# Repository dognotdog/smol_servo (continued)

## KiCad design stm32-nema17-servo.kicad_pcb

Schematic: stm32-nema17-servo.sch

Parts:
C1, C2, C3, C4, C5, C6, C7, C8, C9, C18: 100n; C_0402_1005Metric
C10, C12, C23, C24: 10u 60V; C_1210_3225Metric
C11, C13: 100n 60V; C_0402_1005Metric
C14, C22: 10u 20V; C_0805_2012Metric
C15: 1u 16V; C_0603_1608Metric
C16: 47n 60V; C_0603_1608Metric
C17: 1u 6.3V; C_0402_1005Metric
C19: 22u 5V; C_0805_2012Metric
C20: 100n 16V; C_0402_1005Metric
C21: 100n 20V; C_0402_1005Metric
D1, D2: 1A; D_0402_1005Metric
D3: IN-S128TATRGB; LED_Kingbright_AAA3528ESGCT
D4: 3.3V 1mA; D_0402_1005Metric
H1: M3; MountingHole_3.2mm_M3_DIN965_Pad
H2, H3, H4: M3; MountingHole_3.2mm_M3
J1: Conn_01x05; PinHeader_1x06_P2.54mm_Vertical
J2: C31-S-RA-CS1A-BK-SS; USB_C_Receptacle_Adam_C31-S-RA-CS1A-BK-SS
J3: TC-2050; Tag-Connect_TC2050-IDC-NL_2x05_P1.27mm_Vertical
J4, J5: Screw_Terminal_01x02; TerminalBlock_Phoenix_PT-1,5-2-3.5-H_1x02_P3.50mm_Horizontal
J7, J8: Conn_01x03; PinHeader_1x03_P2.54mm_Vertical
J9: Conn_01x02; PinHeader_1x02_P2.54mm_Vertical
L1, L3: BLM18PG471SN1D; L_0603_1608Metric
L2: 2.2uH 1.6A; L_0806_2016Metric
L4: 22uH 1.6A; L_Taiyo-Yuden_NR-50xx
M1: Stepper_Motor_bipolar; PinHeader_1x04_P2.54mm_Vertical
Q1: NTTFS4937N; WDFN8
Q2, Q3, Q4, Q5, Q6, Q7: NVTFS5C658NL; WDFN8
Q8, Q9, Q10: SSM3K35CTC; SOT-883
R1, R2, R3: 680R; R_0402_1005Metric
R4, R5: 5K1; R_0402_1005Metric
R6: 2.2R; R_0402_1005Metric
R7, R8, R27: 100K; R_0402_1005Metric
R9, R10, R11: 15m; R_1206_3216Metric
R12, R28: 120K; R_0402_1005Metric
R13: 10K; R_0402_1005Metric
R14, R15, R16: 100R; R_0402_1005Metric
R17: 430R; R_0402_1005Metric
R18, R19: 470R; R_0402_1005Metric
R20, R21, R22, R23, R24, R25, R26: 1K; R_0402_1005Metric
R29: 5K; R_0402_1005Metric
SW1: EVP-BB2A9B000; SW_SPST_EVPBB
U1: STM32G431CBU; QFN-48-1EP_7x7mm_P0.5mm_EP5.6x5.6mm_ThermalVias
U2: 74LVC2G32; X2SON-8_1.4x1mm_P0.35mm
U3: UCC27516; Texas_PWSON-N6
U4: AS5047D; TSSOP-14_4.4x5mm_P0.65mm-inlaid
U5: TPS62172DSG; WSON-8-1EP_2x2mm_P0.5mm_EP0.9x1.6mm_ThermalVias
U6: DRV8323RS; VQFN-48_EP_6.8x6.8_Pitch0.5mm

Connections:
+3.3VA: C5.1, L3.2, U1.21 (VDDA)
+3V3: C1.1, C2.1, C3.2, C4.2, C7.1, C9.1, C19.1, J1.3, J3.1 (VTref), L2.2, L3.1, R8.1, R27.2, U1.1 (VBAT), U1.23 (VDD), U1.35 (VDD), U1.48 (VDD), U2.8 (VCC), U4.11 (VDD), U4.12 (VDD3), U5.6 (VOS)
/BUCK_CB: C20.1, U6.44 (CB)
/BUCK_FB: R12.2, R13.1, U6.1 (FB)
/BUCK_SW: C20.2, D2.1 (K), L4.1, U6.45 (SW)
ASCS: U2.3, U4.1 (~CS)
ASEL: U1.22 (PB10), U2.6
DM: J2.A7 (D-), J2.B7 (D-), U1.33 (PA11)
DP: J2.A6 (D+), J2.B6 (D+), U1.34 (PA12)
DRVCS: U2.7, U6.32 (GAIN/~SCS)
DRVEN: U1.15 (PA7), U6.33 (ENABLE)
DRVFAULT: U1.16 (PC4), U6.28 (~FAULT)
DRVSEL: U1.29 (PC6), U2.2
ENA: U1.19 (PB2), U6.38 (INLA)
ENB: U1.18 (PB1), U6.40 (INLB)
ENC: U1.17 (PB0), U6.42 (INLC)
ENCA: R21.1, U1.42 (PB4)
ENCB: R22.1, U1.43 (PB5)
ENCI: R20.1, U1.41 (PB3)
GND: C1.2, C2.2, C3.1, C4.1, C5.2, C6.2, C7.2, C8.1, C9.2, C10.2, C11.2, C12.2, C13.2, C14.2, C17.2, C18.2, C19.2, C21.2, C22.2, C23.2, C24.2, D2.2 (A), D4.2 (A), H1.1, J1.1, J2.A1 (GND), J2.A12 (GND), J2.B1 (GND), J2.B12 (GND), J3.3 (GND), J3.5 (GND), J3.9 (GNDDetect), J4.2, J7.1, J8.1, J9.1, L1.2, Q1.1-3 (S), Q8.2 (S), Q9.2 (S), Q10.2 (S), R1.1, R2.1, R3.1, R4.1, R5.1, R9.2, R10.2, R11.2, R13.2, R29.2, SW1.1, U1.49 (VSS/PAD), U2.4 (GND), U3.1 (IN-), U3.2 (GND), U3.3 (GND), U3.7 (PAD), U4.5 (TEST), U4.13 (GND), U5.1 (PGND), U5.4 (AGND), U5.5 (FB), U5.9 (PAD), U6.2 (PGND), U6.12 (SNA), U6.13 (SNB), U6.22 (SNC), U6.27 (DGND), U6.35 (AGND), U6.43 (BGND), U6.49 (PAD/GND)
GR: Q1.4 (G), R6.1
LEDB: R14.2, U1.46 (PB8/BOOT0)
LEDG: R15.2, U1.44 (PB6)
LEDR: R16.2, U1.45 (PB7)
MISO: U1.27 (PB14), U4.3 (MISO), U6.29 (MODE/SDO)
MOSI: U1.28 (PB15), U4.4 (MOSI), U6.30 (IDRIVE/SDI)
NRST: J3.10 (~RESET~), R27.1, SW1.2, U1.7 (PG10/NRST)
NSS: U1.25 (PB12), U2.1, U2.5
unnamed: C6.1, U1.20 (VREF+)
unnamed: C15.2, U6.5 (VCP)
unnamed: C16.1, U6.4 (CPH)
unnamed: C16.2, U6.3 (CPL)
unnamed: C17.1, U6.36 (DVDD)
unnamed: C18.1, U6.26 (VREF)
unnamed: D1.2 (A), J2.A4 (VBUS), J2.A9 (VBUS), J2.B4 (VBUS), J2.B9 (VBUS)
unnamed: D3.1, R17.1
unnamed: D3.2, R18.1
unnamed: D3.3, R19.1
unnamed: J1.4, R1.2, R20.2
unnamed: J1.5, R2.2, R21.2
unnamed: J1.6, R3.2, R22.2
unnamed: J2.A5 (CC1), R4.2
unnamed: J2.B5 (CC2), R5.2
unnamed: J2.S1 (SHIELD), L1.1
unnamed: J7.2, R23.2
unnamed: J7.3, R24.2
unnamed: J8.2, R25.2
unnamed: J8.3, R26.2
unnamed: L2.1, U5.7 (SW)
unnamed: Q2.4 (G), U6.8 (GHA)
unnamed: Q3.4 (G), U6.10 (GLA)
unnamed: Q4.4 (G), U6.17 (GHB)
unnamed: Q5.4 (G), U6.15 (GLB)
unnamed: Q6.4 (G), U6.18 (GHC)
unnamed: Q7.4 (G), U6.20 (GLC)
unnamed: Q8.1 (G), R14.1
unnamed: Q8.3 (D), R17.2
unnamed: Q9.1 (G), R15.1
unnamed: Q9.3 (D), R18.2
unnamed: Q10.1 (G), R16.1
unnamed: Q10.3 (D), R19.2
unnamed: R6.2, U3.5 (OUT)
unnamed: R7.1, U6.48 (~SHDN)
unnamed: R8.2, U5.8 (PG)
OA: M1.1, Q2.1-3 (S), Q3.5-8 (D), U6.9 (SHA)
OB: M1.2, M1.3, Q4.1-3 (S), Q5.5-8 (D), U6.16 (SHB)
OC: M1.4, Q6.1-3 (S), Q7.5-8 (D), U6.19 (SHC)
OR: J5.2, Q1.5-8 (D)
PWMA: U1.11 (PA3), U6.37 (INHA)
PWMB: U1.10 (PA2), U6.39 (INHB)
PWMC: U1.9 (PA1), U6.41 (INHC)
PWMR: U1.8 (PA0), U3.6 (IN+)
RA: Q3.1-3 (S), R9.1, U6.11 (SPA)
RB: Q5.1-3 (S), R10.1, U6.14 (SPB)
RC: Q7.1-3 (S), R11.1, U6.21 (SPC)
RX1: R24.1, U1.32 (PA10)
SCL3: R25.1, U1.30 (PA8)
SDA3: R26.1, U1.40 (PC11)
SLCK: U1.26 (PB13), U4.2 (SCK), U6.31 (VDS/SCLK)
SOA: U1.12 (PA4), U6.25 (SOA)
SOB: U1.13 (PA5), U6.24 (SOB)
SOC: U1.14 (PA6), U6.23 (SOC)
SWCLK: J3.4 (SWDCLK/TCK), U1.37 (PA14)
SWDIO: J3.2 (SWDIO/TMS), U1.36 (PA13)
SYNC: J9.2, U1.47 (PB9)
TX1: R23.1, U1.31 (PA9)
VBUS: C10.1, C11.1, C12.1, C13.1, C15.1, C23.1, C24.1, J4.1, J5.1, Q2.5-8 (D), Q4.5-8 (D), Q6.5-8 (D), R7.2, R28.1, U6.6 (VM), U6.7 (VDRAIN), U6.47 (VIN)
VBUSDIV: D4.1 (K), R28.2, R29.1, U1.24 (PB11)
VDD: C8.2, C14.1, C21.1, C22.1, D1.1 (K), D3.4, J1.2, L4.2, R12.1, U3.4 (VDD), U5.2 (VIN), U5.3 (EN)

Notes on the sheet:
DRV8323 cannot be daisy-chained on SPI
4937N (30V) can do 8A continuous current on minimal pad in thermal limit NVTFS5C658NL is a similar 60V part
Sense Resistors: 1206 can dissipate 1.5W, use 1W to be conservative Rmax = 1W / 8A^2 = 15.6 mOhm
V0.2: VBUS feedback

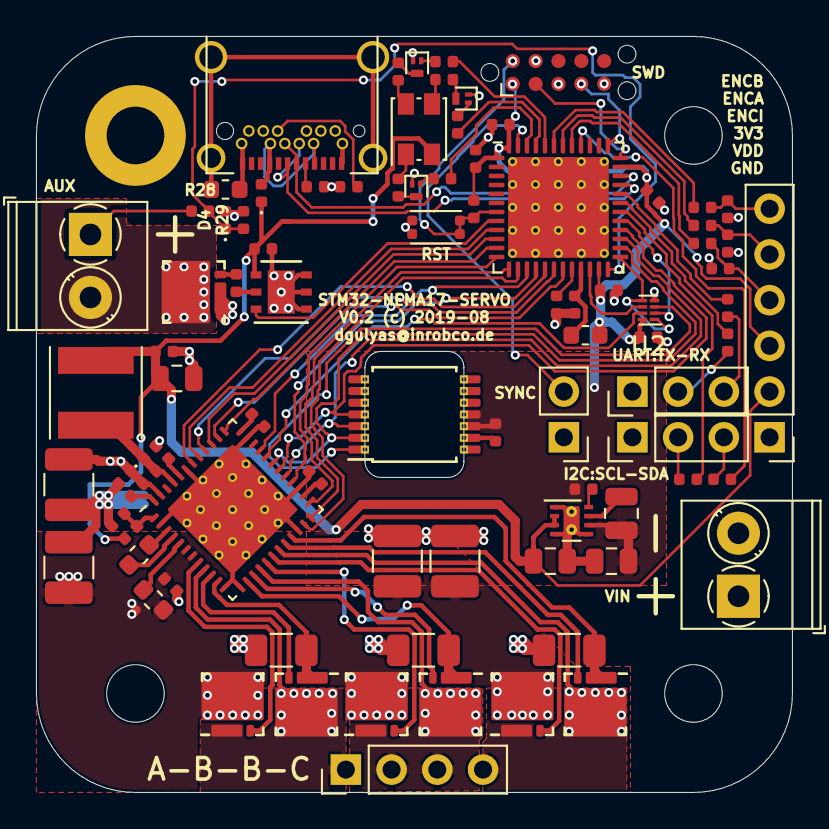
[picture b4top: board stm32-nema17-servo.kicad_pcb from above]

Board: 2 copper layers, 42.0 x 42.0 mm, 91 parts (0 on the bottom side), 89 nets.

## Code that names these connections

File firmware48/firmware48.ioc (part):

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Mcu.Name=STM32G431C(6-8-B)Ux
Mcu.Package=UFQFPN48
Mcu.UserName=STM32G431CBUx
PA0.GPIOParameters=GPIO_Speed
PA0.GPIO_Speed=GPIO_SPEED_FREQ_VERY_HIGH
PA0.Signal=S_TIM2_CH1
PA1.GPIOParameters=GPIO_Speed
PA1.GPIO_Speed=GPIO_SPEED_FREQ_VERY_HIGH
PA1.Signal=S_TIM2_CH2
PA10.Mode=Asynchronous
PA10.Signal=USART1_RX
PA11.GPIOParameters=GPIO_Speed
PA11.GPIO_Speed=GPIO_SPEED_FREQ_VERY_HIGH
PA11.Mode=Device
PA11.Signal=USB_DM
PA12.GPIOParameters=GPIO_Speed
PA12.GPIO_Speed=GPIO_SPEED_FREQ_VERY_HIGH
PA12.Mode=Device
PA12.Signal=USB_DP
PA13.Mode=Serial_Wire
PA13.Signal=SYS_JTMS-SWDIO
PA14.Mode=Serial_Wire
PA14.Signal=SYS_JTCK-SWCLK
PA2.GPIOParameters=GPIO_Speed
PA2.GPIO_Speed=GPIO_SPEED_FREQ_VERY_HIGH
PA2.Signal=S_TIM2_CH3
PA3.GPIOParameters=GPIO_Speed
PA3.GPIO_Speed=GPIO_SPEED_FREQ_VERY_HIGH
PA3.Signal=S_TIM2_CH4
PA4.Mode=IN17-Single-Ended
PA4.Signal=ADC2_IN17
PA5.Mode=IN13-Single-Ended
PA5.Signal=ADC2_IN13
PA6.Mode=IN3-Single-Ended
PA6.Signal=ADC2_IN3
PA7.GPIOParameters=GPIO_Speed
PA7.GPIO_Speed=GPIO_SPEED_FREQ_VERY_HIGH
PA7.Signal=GPIO_Output
PA8.GPIOParameters=GPIO_Pu
PA8.GPIO_Pu=GPIO_PULLUP
PA8.Mode=I2C
PA8.Signal=I2C3_SCL
PA9.Mode=Asynchronous
PA9.Signal=USART1_TX
PB0.GPIOParameters=GPIO_Speed
PB0.GPIO_Speed=GPIO_SPEED_FREQ_VERY_HIGH
PB0.Signal=GPIO_Output
PB1.GPIOParameters=GPIO_Speed
PB1.GPIO_Speed=GPIO_SPEED_FREQ_VERY_HIGH
PB1.Signal=GPIO_Output
PB10.GPIOParameters=GPIO_Speed,PinState
PB10.GPIO_Speed=GPIO_SPEED_FREQ_VERY_HIGH
PB10.PinState=GPIO_PIN_SET
PB10.Signal=GPIO_Output
PB11.Mode=IN14-Single-Ended
PB11.Signal=ADC1_IN14
PB12.GPIOParameters=GPIO_Speed
PB12.GPIO_Speed=GPIO_SPEED_FREQ_VERY_HIGH
PB12.Mode=NSS_Signal_Hard_Output
PB12.Signal=SPI2_NSS
PB13.GPIOParameters=GPIO_Speed
PB13.GPIO_Speed=GPIO_SPEED_FREQ_VERY_HIGH
PB13.Mode=Full_Duplex_Master
PB13.Signal=SPI2_SCK
PB14.GPIOParameters=GPIO_Speed,GPIO_PuPd
PB14.GPIO_PuPd=GPIO_NOPULL
PB14.GPIO_Speed=GPIO_SPEED_FREQ_VERY_HIGH
PB14.Mode=Full_Duplex_Master
PB14.Signal=SPI2_MISO
PB15.GPIOParameters=GPIO_Speed
PB15.GPIO_Speed=GPIO_SPEED_FREQ_VERY_HIGH
PB15.Mode=Full_Duplex_Master
PB15.Signal=SPI2_MOSI
PB2.GPIOParameters=GPIO_Speed
PB2.GPIO_Speed=GPIO_SPEED_FREQ_VERY_HIGH
PB2.Signal=GPIO_Output
PB3.GPIOParameters=GPIO_Speed
PB3.GPIO_Speed=GPIO_SPEED_FREQ_VERY_HIGH
PB3.Signal=S_TIM3_ETR
PB4.GPIOParameters=GPIO_Speed
PB4.GPIO_Speed=GPIO_SPEED_FREQ_VERY_HIGH
PB4.Signal=S_TIM3_CH1
PB5.GPIOParameters=GPIO_Speed
PB5.GPIO_Speed=GPIO_SPEED_FREQ_VERY_HIGH
PB5.Signal=S_TIM3_CH2
PB6.GPIOParameters=GPIO_Speed
PB6.GPIO_Speed=GPIO_SPEED_FREQ_VERY_HIGH
PB6.Signal=S_TIM4_CH1
PB7.GPIOParameters=GPIO_Speed
PB7.GPIO_Speed=GPIO_SPEED_FREQ_VERY_HIGH
PB7.Signal=S_TIM4_CH2
PB8-BOOT0.GPIOParameters=GPIO_Speed
PB8-BOOT0.GPIO_Speed=GPIO_SPEED_FREQ_VERY_HIGH
PB8-BOOT0.Signal=S_TIM4_CH3
PB9.GPIOParameters=GPIO_Speed
PB9.GPIO_Speed=GPIO_SPEED_FREQ_VERY_HIGH
PB9.Signal=S_TIM4_CH4
PC11.GPIOParameters=GPIO_Pu
PC11.GPIO_Pu=GPIO_PULLUP
PC11.Mode=I2C
PC11.Signal=I2C3_SDA
PC4.GPIOParameters=GPIO_PuPd
PC4.GPIO_PuPd=GPIO_PULLUP
PC4.Signal=GPIO_Input
PC6.GPIOParameters=GPIO_Speed,PinState
PC6.GPIO_Speed=GPIO_SPEED_FREQ_VERY_HIGH
PC6.PinState=GPIO_PIN_SET
PC6.Signal=GPIO_Output
PF0-OSC_IN.Mode=IN10-Single-Ended
PF0-OSC_IN.Signal=ADC1_IN10
RCC.HSE_VALUE=8000000
RCC.SYSCLKFreq_VALUE=170000000
RCC.SYSCLKSource=RCC_SYSCLKSOURCE_PLLCLK
board=custom

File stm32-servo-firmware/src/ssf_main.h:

#ifndef SSF_MAIN_H
#define SSF_MAIN_H

#include "ssf_scheduler.h"

#if defined(STM32G431xx) || defined(STM32G491xx)
#include "stm32g4xx_hal.h"
#endif

#include <stdint.h>
#include <math.h>
#include <stddef.h>






extern ADC_HandleTypeDef hadc1;
extern ADC_HandleTypeDef hadc2; // current sense
extern DMA_HandleTypeDef hdma_adc1;
extern DMA_HandleTypeDef hdma_adc2;


extern TIM_HandleTypeDef htim2;	// 3 Phase + Brake Resistor PWM
extern TIM_HandleTypeDef htim3;	// ABI Encoder Input
extern TIM_HandleTypeDef htim4;	// RGB LED

extern TIM_HandleTypeDef htim1;	// TIM2 event counter
extern TIM_HandleTypeDef htim6; // us timer

extern TIM_HandleTypeDef htim15;	// current sense offset
extern TIM_HandleTypeDef htim16;	// SPI timing

#define ADC1_NOMINAL_MAXCOUNT 		4095
#define ADC1_SHIFT					4
#define ADC1_OVERSAMPLING_COUNT		256
#define ADC1_OVERSAMPLING_FACTOR	(ADC1_OVERSAMPLING_COUNT >> ADC1_SHIFT)

#define ADC2_NOMINAL_MAXCOUNT 		4095
#define ADC2_SHIFT					0
// #define ADC2_OVERSAMPLING_COUNT		16
// #define ADC2_OVERSAMPLING_FACTOR	(ADC2_OVERSAMPLING_COUNT >> ADC2_SHIFT)



#if SSF_HARDWARE_VERSION <= 0x00000600
	#define PIN_DRVEN		GPIOA, GPIO_PIN_7
	#define PIN_ENA			GPIOB, GPIO_PIN_2
	#define PIN_ENB			GPIOB, GPIO_PIN_1
	#define PIN_ENC			GPIOB, GPIO_PIN_0

	#define HTIM_LED 		(&htim4)
	#define HTIM_ENC 		(&htim3)
	#define HTIM_DRV 		(&htim2)
	#define HTIM_ISENSE_OFFSET	(&htim15)
	#define HTIM_SPI		(&htim16)
#else
	#error oops, dont have peripheral defs for this hardware version
#endif

typedef enum {
	HTIM_DRV_CH_R = TIM_CHANNEL_1,
	HTIM_DRV_CH_A = TIM_CHANNEL_4,
	HTIM_DRV_CH_B = TIM_CHANNEL_3,
	HTIM_DRV_CH_C = TIM_CHANNEL_2
} mctrl_pwmChannelId_t;




extern ssf_scheduledTask_t tasks[SCHED_COUNT];

extern void ssf_init(void);
extern void ssf_idle(void);

extern void ssf_analogInit(void);
extern void ssf_analogStartRealtime(void);
extern void ssf_analogStopRealtime(void);
extern float ssf_getVbus(void);
extern float ssf_getVddp(void);
extern float ssf_getVdda(void);


extern void ssf_ledInit(void);
extern void ssf_ledIdle(void);

extern void spwm_init(void);
extern void spwm_startRealtime(void);
extern void spwm_stopRealtime(void);

extern void spwm_idle(void);
extern uint16_t spwm_setDrvChannel(mctrl_pwmChannelId_t ch, float normValue);
extern void spwm_enableHalfBridges(uint32_t outputMask);

extern void ssf_ui1sTask(uint32_t now_us);
// void ssf_adc2IrqHandler(ADC_HandleTypeDef *hadc);

extern void ssf_usbRxCallback(const void* data, size_t datalen);

extern void 	ssfa_isenseAnalogInit(void);
extern float 	ssfa_isenseCountToNormalized(uint32_t adcCount);
extern float 	ssfa_isenseMaxCount(void);

extern uint32_t ssfa_isenseAdcTimerOffset(void);
extern void 	ssfa_configMotorDriverCurrentAnalogChannels(void);

extern float sintab(float x);

static inline float fclampf(float a, float minv, float maxv)
{
	return fminf(fmaxf(a, minv), maxv);
}

static inline uint32_t umin(uint32_t const a, uint32_t const b)
{
	return a < b ? a : b;
}

static inline uint32_t umax(uint32_t const a, uint32_t const b)
{
	return a > b ? a : b;
}

static inline uint32_t uclamp(uint32_t a, uint32_t minv, uint32_t maxv)
{
	return umin(umax(a, minv), maxv);
}


#endif // SSF_MAIN_H

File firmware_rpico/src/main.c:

/**
 * 
 */

#include <stdio.h>

#include "pico/stdlib.h"
#include "pico/binary_info.h"
#include "pico/critical_section.h"
#include "pico/multicore.h"

#include "hardware/i2c.h"
#include "hardware/structs/busctrl.h"
#include "hardware/structs/accessctrl.h"
#include "hardware/structs/powman.h"
#include "hardware/structs/watchdog.h"

#include "smol_servo.h"
#include "smol_fs.h"
#include "smol_isense_cal.h"
#include "smol_config.h"
#include "smol_console.h"
#include "pico_debug.h"

#include "fusb302.h"
#include "tmc6200.h"


void i2c_fusb_init(void) {
    i2c_init(FUSB_I2C, 100 * 1000);
    gpio_set_function(FUSB_I2C_SDA_PIN, GPIO_FUNC_I2C);
    gpio_set_function(FUSB_I2C_SCL_PIN, GPIO_FUNC_I2C);
    gpio_pull_up(FUSB_I2C_SDA_PIN);
    gpio_pull_up(FUSB_I2C_SCL_PIN);
    // Make the I2C pins available to picotool
    bi_decl(bi_2pins_with_func(FUSB_I2C_SDA_PIN, FUSB_I2C_SCL_PIN, GPIO_FUNC_I2C));

}

void smol_hires_time_init(void) {
	// use a critical section to block IRQs, at least
	// this should not be called once the second core is up
	critical_section_t cr;
	critical_section_init(&cr);
	critical_section_enter_blocking(&cr);
	timer_hw_t *timer_us = timer0_hw;
	timer_hw_t *timer_sysclk = timer1_hw;



	// pause timers
	bool was_paused = timer_us->pause;
	timer_us->pause = 1;
	timer_sysclk->pause = 1;

	// set 2nd timer to sysclk
	timer_sysclk->source = 1;
	// set time to match 1MHz timer
	uint64_t time_us = timer_us->timelr;
	time_us = (time_us << 32) | timer_us->timehr;
	// looking at runtime_init_clocks(), default is 150MHz, we'll just go with that
	uint64_t time_sysclk = time_us * 150u;
	timer_sysclk->timelw = time_sysclk;
	timer_sysclk->timehw = time_sysclk >> 32;

	// unpause both timers with hopefully negligible delay
	timer_us->pause = was_paused;
	timer_sysclk->pause = was_paused;

	critical_section_exit(&cr);
	critical_section_deinit(&cr);
}

#define LED_PIN 8

// Initialize the GPIO for the LED
void pico_led_init(void) {
    // A device like Pico that uses a GPIO for the LED will define PICO_DEFAULT_LED_PIN
    // so we can use normal GPIO functionality to turn the led on and off
    gpio_init(LED_PIN);
    gpio_set_dir(LED_PIN, GPIO_OUT);
}

// Turn the LED on or off
void pico_set_led(bool led_on) {
    // Just set the GPIO on or off
    gpio_put(LED_PIN, led_on);
}

// set by core 1 after its init: from then on core 1 has no XIP access, and core 0 can write the flash
static volatile bool _core1_ram_only = false;

bool smol_core1_is_ram_only(void) {
	return _core1_ram_only;
}

static void __not_in_flash_func(_core1_init)(void) {
	// // mess with AHB priorities
	// uint32_t prio = busctrl_hw->priority;
	// // increase Core1 bus priority
	// prio = BUSCTRL_BUS_PRIORITY_PROC1_BITS;
	// busctrl_hw->priority = prio;

	// core 1 init only. We are not starting the loop until later in main(), once the initialization from code in Flash memory is done, and all code is RAM-only that executes on core 1.
	smol_servo_loop_init();


	// disable FLASH access for CORE 1 so we don't get XIP data stalls
	hw_clear_bits(&accessctrl_hw->xip_main, 0xACCE0000 | ACCESSCTRL_XIP_MAIN_CORE1_BITS);
	__dmb();
	_core1_ram_only = true;

	while (1) {
		smol_servo_loop_idle_core1();
	}
}

int main(int argc, char const *argv[])
{
	smol_hires_time_init();

    stdio_init_all();
    pico_led_init();

    // Make the SPI pins available to picotool
    bi_decl(bi_3pins_with_func(DRV_MISO_PIN, DRV_MOSI_PIN, DRV_SLCK_PIN, GPIO_FUNC_SPI));
    // Make the CS pin available to picotool
    bi_decl(bi_1pin_with_name(DRV_NSS_PIN, "DRV_SPI CS"));

    tmc6200_spi_init(DRV_SPI, DRV_MOSI_PIN, DRV_NSS_PIN, DRV_SLCK_PIN, DRV_MISO_PIN);
	// TMC6200 registers with DRV_EN low, no log output (approx. 0.5ms). The enable waits for the PD contract.
	smol_drv_init();

	// USB PD before all log output and slow init: VBUS is the only power supply. If the sink does not reply to Source_Capabilities in time, the Source sends Hard Reset and removes VBUS, and the board starts again.
	i2c_fusb_init();
	fusb302_init(FUSB_I2C, FUSB_INT_PIN);
	smol_usb_pd_init();
	smol_usb_pd_run_startup();

	// reset cause of this boot: POWMAN CHIP_RESET has the HAD_* flags (HAD_POR = power-on reset), WATCHDOG REASON tells a watchdog reset
	info_println("reset cause: CHIP_RESET 0x%08x, WATCHDOG REASON 0x%x", powman_hw->chip_reset, watchdog_hw->reason);
	smol_drv_log_status();

	// mount only: a format erases flash, and core 0 then cannot answer PD messages. smol_fs_run() does a necessary format later.
	smol_fs_init();
	// config file: applies the current sense gain to the TMC6200 (DRV_EN is still low). Without a mounted FS, smol_fs_run() loads the config after the deferred format.
	// current sense offset table (needs the gain from the config)
	if (smol_fs_is_mounted()) {
		smol_config_load();
		smol_isense_cal_load();
	}

	multicore_reset_core1();
	multicore_launch_core1(_core1_init);

	bool led = false;
	bool loop_started = false;
	while (1) {
		picobug_process_core1_queue();

		// servo loop start at boot, after the core 1 init: zero calibration with DRV_EN low, then the idle state OFF (bridge off)
		if (!loop_started && smol_core1_is_ram_only()) {
			smol_servo_loop_start();
			loop_started = true;
		}

		int ch = getchar_timeout_us(0);
		if (ch >= 0) {
			smol_console_process_char(ch);
		}

		smol_usb_pd_run();
		smol_drv_run();
		smol_fs_run();

		smol_servo_loop_idle_core0();

		// pico_set_led(led = !led);
		// uint64_t t_fast = timer_time_us_64(timer1_hw);
		// dbg_time_t tt = {.seconds = t_fast / 1000000u, .microseconds = t_fast % 1000000u};
		// dbg_println("foo %" PRIu32 ".%06" PRIu32, tt.seconds, tt.microseconds);
		// sleep_ms(1000);
		// printf("foo\n");
	}
	return 0;
}

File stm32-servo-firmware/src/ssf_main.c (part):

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
void test_chipSelects(void)
{
	_setPinAsGpioOutput(PIN_DRVSEL);
	_setPinAsGpioOutput(PIN_ASEL);
	// _setPinAsGpioOutput(PIN_SPI_NSS);

	// HAL_GPIO_WritePin(PIN_SPI_NSS, GPIO_PIN_RESET);
	// HAL_GPIO_WritePin(PIN_DRVSEL, GPIO_PIN_RESET);
	// HAL_GPIO_WritePin(PIN_ASEL, GPIO_PIN_RESET);
	// HAL_Delay(250);
	// HAL_GPIO_WritePin(PIN_DRVSEL, GPIO_PIN_SET);
	// HAL_Delay(250);
	// HAL_GPIO_WritePin(PIN_ASEL, GPIO_PIN_SET);
	// HAL_Delay(250);

	// HAL_GPIO_WritePin(PIN_SPI_NSS, GPIO_PIN_SET);
	// HAL_GPIO_WritePin(PIN_DRVSEL, GPIO_PIN_RESET);
	// HAL_GPIO_WritePin(PIN_ASEL, GPIO_PIN_RESET);
	// HAL_Delay(250);
	// HAL_GPIO_WritePin(PIN_DRVSEL, GPIO_PIN_SET);
	// HAL_Delay(250);
	// HAL_GPIO_WritePin(PIN_ASEL, GPIO_PIN_SET);
	// HAL_Delay(250);

	// HAL_GPIO_WritePin(PIN_SPI_NSS, GPIO_PIN_RESET);
	HAL_GPIO_WritePin(PIN_DRVSEL, GPIO_PIN_SET);
	HAL_GPIO_WritePin(PIN_ASEL, GPIO_PIN_RESET);
	HAL_Delay(50);
	HAL_GPIO_WritePin(PIN_ASEL, GPIO_PIN_SET);
	HAL_Delay(50);
	HAL_GPIO_WritePin(PIN_ASEL, GPIO_PIN_RESET);
	HAL_Delay(50);
	HAL_GPIO_WritePin(PIN_ASEL, GPIO_PIN_SET);
	HAL_Delay(50);

}
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	}
	// // HAL_Delay(8);

	// bool drven = HAL_GPIO_ReadPin(PIN_DRVEN);
	// dbg_println("DRVEN %8u %u", utime_now(), drven);

	// uint32_t adcState = HAL_ADC_GetState(&hadc2);
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
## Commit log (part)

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2019-08-23 Initial commit of NEMA17 form factor servo driver
2019-08-27 board layout improvements and firmware that finally shows up as USB CDC device
2019-08-27 move electronics design files into hardware/ folder
2019-09-08 initial commit of custom mechaduino firmware that boots with Arduino/SAM-BA bootloader
2019-09-10 working constant speed open loop mechaduino stepper driving at constant speed with an interpolated sine lookup
2019-09-11 further progress in bringing up SPI, ADCs, etc
2019-09-11 further fixes on v0.2 hardware
2019-09-11 adds AD5047 readout to mechaduino firmware
2019-09-17 hardware version 0.2 as sent to board fab
2019-09-18 further firmware improvements, including proper scheduling of fast control loop to sync with PWM/ADC and readout of the current feedback signals
2019-09-18 adds missing VREF connections on STM32 and DRV8323
2019-09-24 adds fuse to USB power input to protect both host and device
2019-09-24 motor parameter estimation can now be triggered from USB, and it estimates inductance on each phase via kalman filters
2020-03-31 software updated for V0.2 hardware, with characterization experiments; work on V0.3 hardware fixes
2020-04-01 initial commit for switch to 3rd party UsbDevice lib, so that we can have HID+CDC at the same time, which isn't easily possible with the STM32 library on STM32G4
2020-04-01 improved debug output, now also available over uart
2020-04-01 add additional USBDevice support files
2020-04-01 add buffer size macros for stdin/out over USB
2020-04-01 USB CDC now working with new UsbDevice library
2020-04-02 enable debug output over uart, it is more convenient for naw than through USB
2020-04-02 usb reading/writing now working
2020-04-02 PCB layout improvements
2020-04-02 add sublime project file
2020-04-03 adds HID device with X axis RGB LED control
2020-04-03 add comment about what this file is
2020-04-03 updates sublime project with build settings
2020-04-03 more enhancements for v0.3, discovered that hardware NSS should be usable, after all
2020-04-07 hardware v0.3 as ordered
2020-04-08 futher hardware-v0.3 notes
2020-04-08 add sublime build target for flashing hardware
2020-04-08 updated HAL code generated
2020-04-09 re-generated code v0.2 hardware
2020-04-09 hall sensor now read asynchronously
2020-04-12 fix erroneous timer period for gate driver PWM
2020-04-13 current sense improvements: added more documentation and current sense sampling now centered on PWM phases through offset with TIM15
2020-04-13 SPI handling improvements to prevent race conditions
2020-04-22 updated codegen for v0.3 hardware; I/O settings tweaks
2020-04-22 reduce min heap size again in linker script, don't know how it got there as we typically don't want heap at all
2020-04-22 disable USB init from HAL through ifdef in user code instead of comments, add TIM1 init as event counter, and fix ADC clock source
2020-04-22 add TIM1 initialization as event counter for ADC triggering
2020-04-22 update analog readout to include VDDP and compensation factors
2020-04-22 start TIM1 for event counting
2020-04-22 add function to enable motor driver half bridges individually
2020-04-22 fix perf header to include event counting
2020-04-22 add missing perf counter modules
2020-04-22 add utility functions to main header
2020-04-22 improved debug output
2020-04-22 improvements and experiments with system identification: added linear regression function, and fixed up some formulas
2020-04-22 updated design docs
2020-04-23 add ADC sampling offset for current sensing
2020-04-23 add warning level debug message support
2020-04-23 adjust VBUS and VDDP readouts to compensate for parasitic resistances
2020-04-23 change system identification to use static method for resistance, and dynamic for impedance, as dynamic is terrible for impedance due to noise; add collect vbus readouts during identification in addi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
2020-04-23 factor out linear regression into own module
2020-04-23 add missing math header includes for factored out linreg code
2020-04-23 enable proper task scheduling for idle loop
2020-04-23 cosmetic updates to schematic and board
2020-04-23 add program target for sublime build system
2020-04-24 add TIM16 for SPI timing
2020-04-24 add delay-less SPI NSS pulse timing with TIM16; refactor mctrl a bit
2020-04-24 slight refactoring of mctrl sysid to deal with vbus better
2020-04-24 start on framework for storing configuration data in flash
2020-04-25 fix sine table lookup, it was ggiving wrong values before, now interpolation seems correct
2020-04-25 had to add 'reset halt' to rst target to reliably restart MCU, otherwise it would sometimes get stuck in calibration, but the bug cannot be reproduced with the debugger attached
2020-04-25 add impedance based inductance estimation, which seems to give a better estimate than di/dt based
2020-04-25 rename PHASE identification step to IMPEDANCE
2020-04-26 fix ADC trigger offseting
2020-04-26 oversampling mode for ADC2 now set based on header macros, so we don't have through stm32cube codegen for changes
2020-04-26 remove bit shift for ADC2, as it's not strictly necessary
2020-04-26 add debug printf function to be able to output partial lines, for data mainly
2020-04-27 chang AS5047 NSS pin to start high on reset, enable OC preload for SPI timer
2020-04-27 add module for DSP functions
2020-04-27 check parity and r/w bit for AS5047 status
2020-04-27 mctrl improvements and refactoring
2020-04-30 add timestamps to err debug messages
2020-04-30 improved SPI state machine, though still not without quirks
2020-04-30 updated docs with kalman filter design
2020-04-30 remove alpha from simple position estimator
2020-04-30 added stall speed detection for identifying motor constants better
2020-05-01 fix mixup of slope and intercept in linear regression function :/
2020-06-02 v0.3.1 hardware doe not require parasitic correction due to 100n buffer caps
2020-06-02 add estimator source to makefile and add warning flag for checkin array out-of-bounds accesses
2020-06-02 add support for blackmagic probe in makefile
2020-06-04 tweak blackmagic probe makefile targets
2020-06-05 fix bug in SPI state machine that caused an SPI transfer to signal completion before all data was transfered, under certain conditions
2020-06-05 improved SPI API for bug hunting
2020-10-09 update makefile with more warnings and newer compiler
2020-10-09 improved flash debug output
2020-10-09 add uclamp function for clamping uints
2020-10-09 setting a power PWM channel now returns the integer value that was set in hardware
2020-10-09 improve SPI state machine by adding error recovery mechanism when attempting to start transfers
2020-10-09 make mctrl_modAngle avaliable to other modules
2020-10-09 improved encoder errors debugging; improved motor param estimation
2020-10-10 revert change for current calc function proto for now
2020-10-10 unified 2/3 phase pwm calculations
2020-10-10 bugfixes in step size calculation with addition of 3 phase algorithm
2020-10-28 impl of config journal flash file system
2020-10-28 adds cooldown phase for motor driver init errors; improvements for parameter detection
2020-10-28 adds linker script for config flash segment
2020-10-28 removed obsolete usb driver file
2020-10-28 updated driver config with v1.3 HAL package, and some minor fixes in timer and ADC config
2020-10-28 squelch compiler warning by adding default case in switch for unknown channels
2020-10-28 remove FLASH_IRQHandler() definition as it is now enabled in HAL
2020-10-28 extend USB serial console interface to test config flash stuff
2020-10-28 more config flash impl improvements; fix page erase
2020-10-28 fix missing var in page erase
2021-12-29 refactor analog sampling start/stop
2021-12-29 refactor initialization of timers
2021-12-30 v0.3.1 board
2022-01-03 commits missing timer function prototypes in header
2022-01-03 4 layer board design
2022-02-18 add unit testing Makefile skeleton
2022-02-18 more test makefile improvements
2022-02-20 cosmetic updates to some of the pcb footprints, mainly for better 3D models
2022-02-26 tweaks to v0.4.0 hardware design
2022-02-26 adds licensing info
2022-08-06 addition of TMC6200 variant
2022-08-06 updated readme with part variants due to chip shortage
2022-08-06 rearrange TMC6200 version to have MCU closer to driver chip
2022-08-06 v0.6.0 PCB order
2022-08-21 v0.6.1 hardware
2022-08-24 add hardware schematic plots
2022-08-24 add v0.7.0 prelim hardware design with USB Power Delivery
2022-08-24 add STM32G491CEU6 variant build files
2022-08-26 work on tmc6200 bringup; spi reorg; start on cogging characterization
2022-08-31 more SPI work to bypass HAL
2022-09-02 adds fastloop SPI readouts
2022-09-07 kalman filter impl; SPI improvements; analog readout improvements
2022-12-18 add board pictures
2022-12-18 update board picture to be less blurry
2024-08-22 smol-servo RPI2350B variant
2024-08-24 updated RP2350 hardware
2024-08-27 addition of USB-C reverse current protection
2025-10-05 change RP2350 board to JLCPCB spec as they are the only ones who have RP2354B chips at the moment
2025-12-28 RP2350 FW initial commit
2025-12-28 RP2350 split board hardware
2026-01-09 servo loop setup for the second core
2026-01-11 filling out and debugging high freq loops on rpico
2026-01-11 optimizing IRQ handlers
2026-01-17 console, model, USB PD work
2026-01-20 v0.9.1 RP2350 fixes
2026-01-20 USB PD related work (waiting for hardware fix)
2026-01-25 addtion of MAG readout and other improvements
2026-03-08 model updates
2026-03-09 USB PD fixes
